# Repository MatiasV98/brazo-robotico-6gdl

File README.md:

# Brazo robótico de 6 grados de libertad con control Bluetooth

Brazo robótico de seis articulaciones con servomotores MG996R, controlado por un Arduino Nano que
recibe comandos por Bluetooth (HC-05). Se maneja desde una **página web con joysticks y barras** que
funciona en la computadora y en Android. Incluye el firmware, la placa de control diseñada en KiCad,
la carcasa en Fusion 360 y la documentación técnica.

Desarrollado en el marco de una **beca de servicio 2026** del Laboratorio de Técnicas Digitales
(Ingeniería Electrónica, UTN Facultad Regional Paraná), como equipo para la asignatura
**Técnicas Digitales II**.

> **English summary.** Six-degree-of-freedom robotic arm (six MG996R servos) controlled by an Arduino
> Nano over Bluetooth (HC-05), operated from a web panel (Web Serial over Bluetooth) with on-screen
> joysticks, sliders and gamepad support. The firmware moves one joint at a time in 1° steps paced by a
> Timer2 interrupt, enforces per-joint safety limits with an elbow/arm interlock, stores the last
> position in EEPROM and reports the cause of every reset. Includes a custom KiCad PCB, a 3D-printed
> enclosure and technical documentation. Lab project, UTN Paraná, 2026.

> **Importante: alimentar por separado el Arduino y los servos.** Si el Nano toma energía del mismo riel que
> los MG996R, los picos de corriente de los servos lo reinician y el brazo "se cae". Con el Arduino
> alimentado aparte y GND común, los reinicios desaparecieron. Detalle en
> [`docs/alimentacion-y-reinicios.md`](docs/alimentacion-y-reinicios.md).

## Equipo

- **Franco Rufiner**, becario: desarrollo del proyecto.
- **Matias Vicentin**, becario de iniciación a la docencia (Técnicas Digitales I): supervisión
  técnica y revisión del desarrollo; diseño e impresión 3D de la carcasa.

## Panel web de control

[`web/control_brazo.html`](web/control_brazo.html) es una sola página, sin instalación, que se conecta
al HC-05 por Web Serial sobre Bluetooth.

- **Joystick:** el izquierdo mueve Hombro y Brazo; el derecho, Muñeca y Codo. Botones mantenidos para
  Dedos y Mano, regulador de velocidad y opción "un solo servo a la vez". Acepta un control físico
  (Xbox, PlayStation o genérico).
- **Barras:** un deslizador por articulación, con botones de ±5° y atajos de teclado.
- **Botones generales:** Leer estado, Posición inicial, Saludo y **PARADA** (también con Espacio o Esc).
- Funciona con Chrome o Edge en la computadora y con Chrome 138 o posterior en Android. No funciona en
  iPhone ni en Firefox.

**Uso:** emparejar el HC-05 desde el sistema (PIN 1234 o 0000), abrir la página, tocar **Conectar** y
elegir el HC-05. En la computadora se abre con doble clic; en Android tiene que estar publicada en una
dirección https (por ejemplo, con GitHub Pages).

## Firmware

[`firmware/brazo_robusto`](firmware/brazo_robusto/brazo_robusto.ino) es la versión actual:

- **Movimiento progresivo** de 1° cada 15 ms. La interrupción del Timer2 solo marca el tiempo y el
  movimiento se hace en `loop()`, así la rutina de interrupción no corrompe los bytes que recibe el
  SoftwareSerial.
- **Un servo a la vez:** los pedidos se ejecutan en el orden en que llegan, para evitar picos de
  corriente.
- **Seguridad entre Codo y Brazo:** si el Codo está fuera de 60–120°, primero vuelve a ese rango y
  recién después se mueve el Brazo.
- **Secuencias:** Saludo (`S`) y Posición inicial (`I`). La parada o cualquier comando manual las cancela.
- **Diagnóstico de reinicios:** al arrancar informa la causa (brown-out, encendido, reset o watchdog)
  por USB y por Bluetooth.
- **Memoria EEPROM:** guarda la última posición; después de un reinicio vuelve a donde estaba.
- **Uso de RAM:** textos en FLASH con `F()` y sin la clase `String`.
- **Recepción sin bloqueo:** el comando termina con Enter o tras 80 ms sin datos; `X` frena al instante.

Lista de comandos, rangos y conexión del HC-05 en
[`docs/comandos-bluetooth.md`](docs/comandos-bluetooth.md). La versión anterior del firmware y los
programas de prueba están en [`firmware/`](firmware/README.md).

## Hardware

- Arduino Nano (ATmega328P) sobre zócalo, en una PCB propia de 50 × 50 mm, dos capas, componentes
  through-hole.
- 12 conectores para servos (D0 a D11; el brazo usa D3, D5, D6, D9, D10 y D11), conector para el HC-05
  con divisor de tensión en su RX y conector para las entradas analógicas A0 a A7.
- Proyecto de KiCad y archivos de fabricación (Gerber y taladrado) en [`hardware/`](hardware/README.md).
  Lista de materiales en [`docs/Materiales_Brazo_Robotico.txt`](docs/Materiales_Brazo_Robotico.txt).

| Esquemático | PCB (vista 3D) | PCB (cobre, cara inferior) |
|---|---|---|
|  |  |  |

La carcasa que protege la electrónica se diseñó en Fusion 360 ([`cad/`](cad/README.md)) y se imprimió
en PLA en una Bambu Lab A1 del Laboratorio de Técnicas Digitales III:

## Estructura del repositorio

| Carpeta | Contenido |
|---|---|
| [`firmware/`](firmware/README.md) | Firmware actual (`brazo_robusto`), versión anterior y programas de prueba (Arduino IDE). |
| [`web/`](web/control_brazo.html) | Panel web de control. |
| [`hardware/`](hardware/README.md) | Proyecto de KiCad de la placa y archivos de fabricación. |
| [`cad/`](cad/README.md) | Carcasa de la electrónica (Fusion 360). |
| [`docs/`](docs/README.md) | Alimentación, comandos, manual técnico, limitaciones y lista de materiales. |

## Cómo usarlo

1. Armar la placa y conectar los servos según el manual técnico
   (`docs/Manual_Tecnico_Brazo_Robotico.pdf`), con el Arduino alimentado aparte y GND común.
2. Cargar `firmware/brazo_robusto` en el Nano con Arduino IDE (librerías `Servo`, `SoftwareSerial` y
   `EEPROM`, incluidas en el IDE). En clones del Nano, elegir *ATmega328P (Old Bootloader)*.
3. Abrir `web/control_brazo.html` y conectar al HC-05. También se puede controlar con cualquier
   terminal Bluetooth serie enviando los comandos de texto.

## Observaciones

- En la revisión actual de la PCB el Arduino Nano queda montado en posición invertida respecto de la
  prevista: hay que respetar la orientación indicada en el manual. Queda para la próxima revisión, junto
  con separar la alimentación del Nano del riel de los servos.
- Si alguna articulación se mueve al revés en el joystick, se corrige en `const INVERTIR` dentro del HTML.

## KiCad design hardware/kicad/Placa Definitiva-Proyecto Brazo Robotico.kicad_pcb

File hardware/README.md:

# hardware

Diseño de la placa de control del brazo robótico (PCB), realizado en **KiCad 10**.

## Contenido

### `kicad/` — Proyecto de KiCad (archivos fuente)

| Archivo | Descripción |
|---|---|
| `.kicad_pro` | Proyecto |
| `.kicad_sch` | Esquemático |
| `.kicad_pcb` | Diseño de la PCB |

### `fabricacion/` — Archivos de fabricación (Gerber y taladrado)

| Archivo | Descripción |
|---|---|
| `-B_Cu.gbr` | Cobre, cara inferior |
| `-B_Mask.gbr` | Máscara antisoldante, cara inferior |
| `-F_Mask.gbr` | Máscara antisoldante, cara superior |
| `-B_Paste.gbr` | Pasta, cara inferior |
| `-F_Paste.gbr` | Pasta, cara superior |
| `-B_Silkscreen.gbr` | Serigrafía, cara inferior |
| `-F_Silkscreen.gbr` | Serigrafía, cara superior |
| `-Edge_Cuts.gbr` | Contorno de la placa |
| `-PTH.drl` | Taladrado de agujeros metalizados |
| `-NPTH.drl` | Taladrado de agujeros no metalizados |
| `-job.gbrjob` | Datos del trabajo de fabricación |

Todos los archivos comienzan con `Placa Definitiva-Proyecto Brazo Robotico`.

Para abrir el diseño: abrir `kicad/Placa Definitiva-Proyecto Brazo Robotico.kicad_pro` con KiCad 10 o superior.

## La placa

| Característica | Valor |
|---|---|
| Dimensiones | 50 × 50 mm |
| Espesor | 1,6 mm |
| Capas | 2 (todo el ruteo en la cara inferior) |
| Componentes | Through-hole (THT) |

Componentes que aloja:

- **Arduino Nano** (A1), montado en zócalo de tiras hembra 1x15.
- **12 conectores para servos** (tiras hembra 1x3), unidos a los pines D0 a D11. El brazo usa D3, D5, D6, D9, D10 y D11.
- **Conector del módulo Bluetooth HC-05** (tira hembra 1x4: RX, TX, GND, 5V), conectado a D12 y D13.
- **Divisor de tensión** para el RX del HC-05: R1, R2 y R3 de 1 kΩ.
- **Conector de entradas analógicas** A0 a A7 (tira hembra 1x8).

| Articulación | Pin |
|---|---|
| Dedos | D3 |
| Muñeca | D5 |
| Mano | D6 |
| Codo | D9 |
| Brazo | D10 |
| Hombro | D11 |

La guía de conexión completa está en el manual técnico (`docs/Manual_Tecnico_Brazo_Robotico.pdf`) y la lista de materiales en `docs/Materiales_Brazo_Robotico.txt`.

## Observaciones

- Por un error en el diseño de la placa, el **Arduino Nano queda montado en posición invertida** respecto de la orientación prevista. Al armar, respetar la orientación indicada en la Figura 1 del manual. Queda pendiente corregirlo en una próxima revisión.
- Los conectores D0 y D1 comparten pines con el puerto USB del Nano: si se conecta algo en ellos, puede interferir al cargar el programa o al usar el Monitor Serie.

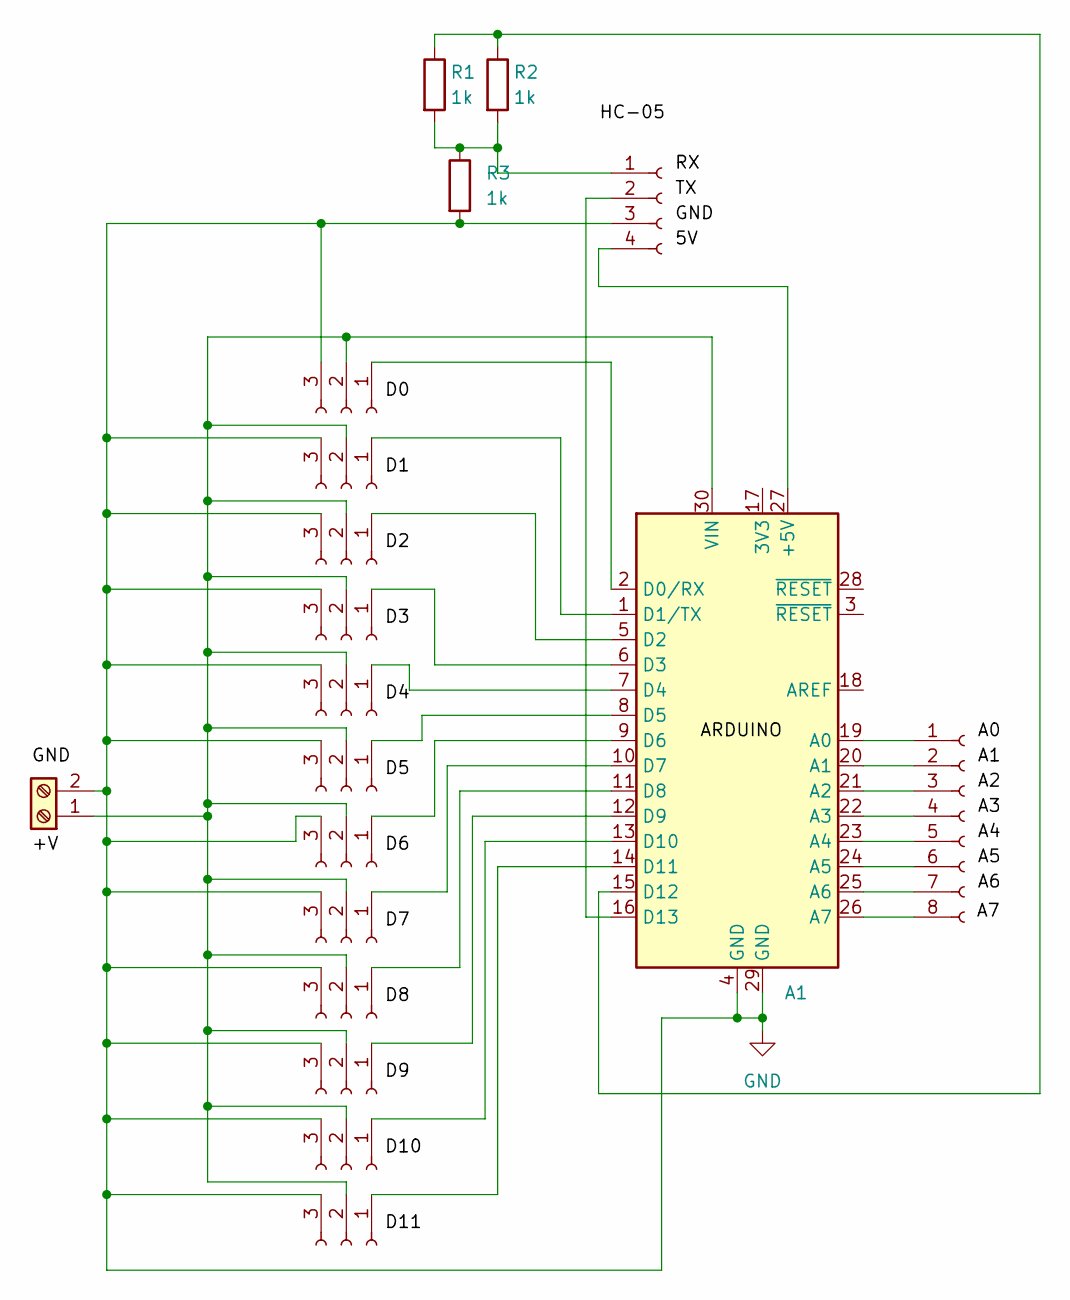
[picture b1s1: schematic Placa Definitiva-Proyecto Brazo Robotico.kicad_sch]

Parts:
A1: Arduino_Nano_v2.x; Arduino_Nano
J1: Screw_Terminal_01x02; TerminalBlock_MaiXu_MX126-5.0-02P_1x02_P5.00mm
J2: Conn_01x04_Socket; PinSocket_1x04_P2.54mm_Vertical
J6: Conn_01x08_Socket; PinSocket_1x08_P2.54mm_Vertical
J11, J12, J13, J14, J15, J16, J17, J18, J19, J20, J21, J22: Conn_01x03_Socket; PinSocket_1x03_P2.54mm_Vertical
R1, R2, R3: 1k; R_Axial_DIN0207_L6.3mm_D2.5mm_P10.16mm_Horizontal

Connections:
GND: A1.4 (GND), A1.29 (GND), J1.2, J2.3, J11.3, J12.3, J13.3, J14.3, J15.3, J16.3, J17.3, J18.3, J19.3, J20.3, J21.3, J22.3, R3.2
unnamed: A1.27 (+5V), J2.4
unnamed: A1.19 (A0), J6.1
unnamed: A1.20 (A1), J6.2
unnamed: A1.21 (A2), J6.3
unnamed: A1.22 (A3), J6.4
unnamed: A1.23 (A4), J6.5
unnamed: A1.24 (A5), J6.6
unnamed: A1.25 (A6), J6.7
unnamed: A1.26 (A7), J6.8
unnamed: A1.2 (D0/RX), J22.1
unnamed: A1.1 (D1/TX), J21.1
unnamed: A1.5 (D2), J20.1
unnamed: A1.6 (D3), J19.1
unnamed: A1.7 (D4), J18.1
unnamed: A1.8 (D5), J17.1
unnamed: A1.9 (D6), J15.1
unnamed: A1.10 (D7), J11.1
unnamed: A1.11 (D8), J12.1
unnamed: A1.12 (D9), J13.1
unnamed: A1.13 (D10), J14.1
unnamed: A1.14 (D11), J16.1
unnamed: A1.15 (D12), R1.1, R2.1
unnamed: A1.16 (D13), J2.2
unnamed: A1.30 (VIN), J1.1, J11.2, J12.2, J13.2, J14.2, J15.2, J16.2, J17.2, J18.2, J19.2, J20.2, J21.2, J22.2
unnamed: J2.1, R1.2, R2.2, R3.1

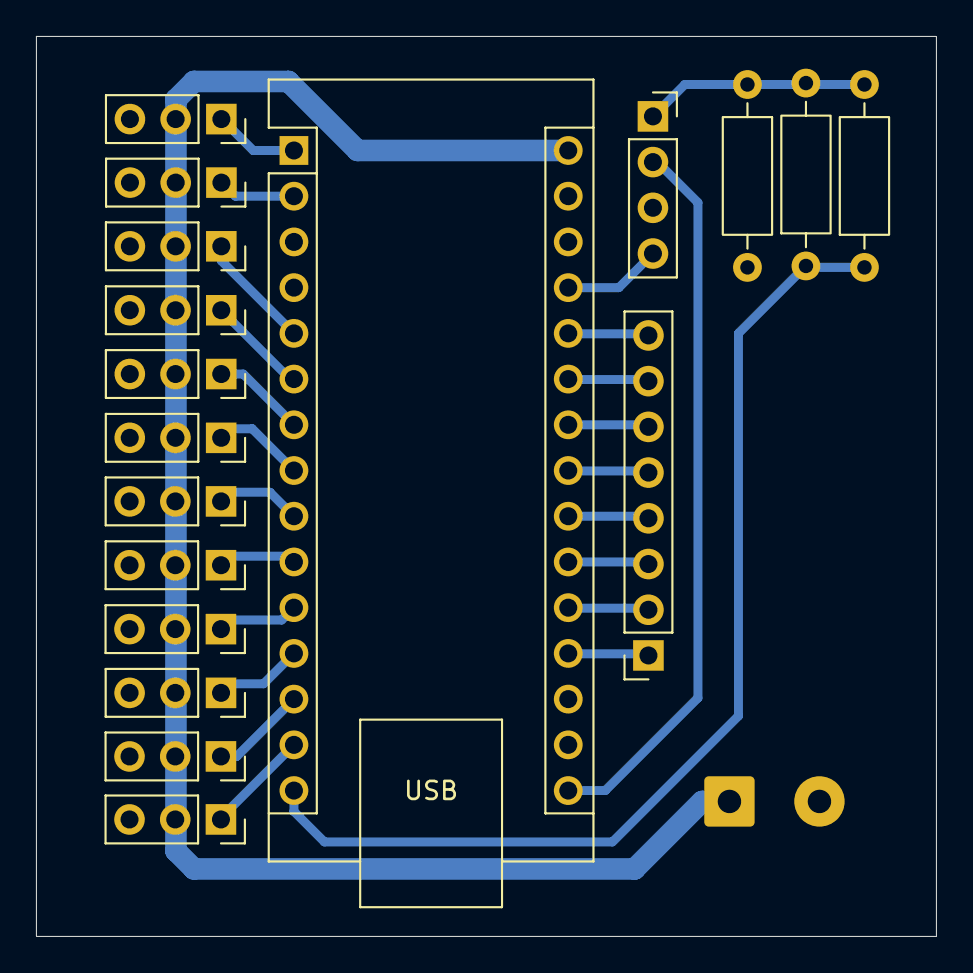
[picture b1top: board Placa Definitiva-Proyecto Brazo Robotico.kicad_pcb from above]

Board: 2 copper layers, 50.0 x 50.0 mm, 19 parts (1 on the bottom side), 26 nets.
